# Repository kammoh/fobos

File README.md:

FOBOS
=====

Flexible Open-source workBench fOr Side-channel analysis (FOBOS) is an "acquisition to analysis" solution which includes all necessary software to control the device under test (attack) (DUT), trigger the oscilloscope, obtain the measurements and analyze them using several power analysis techniques.

FOBOS splits the Side Channel Analysis (SCA) setup into a control board, a DUT, and the SCA workstation. The firmware for the control board can be found in the folder `control`. The hardware description language files required to adapt a cryptographic algorithm to a particular FOBOS DUT are in the folder `DUT`. The `hardware` folder on the other hand contains circuit board design files for FOBOS boards such as the FOBOS Shield and several FOBOS DUTs. The `software` folder contains the scripts to run FOBOS. These python scripts run partially on the SCA workstation within a Jupyter notebook and partially on the Pynq DUT. The `docs` folder contains the FOBOS documentation.

FOBOS Control Board
-------------------
* `control`
   VHDL sources for configuring the FOBOS Control Boards. Requires Xilinx Vivado 2020.2.
   * `basys3ctrl`
     Using a Digilent Inc Basys 3 as control board and an oscilloscope for measurements.
   * `pynqctrl`
     Using a Digilent Inc PYNQ-Z1 as control board and either the FOBOS Shield or an oscilloscope for measurements.
   * `ip-repo` 
     Modules used by either control board.

FOBOS DUT
---------
* `dut`
  VHDL sources for FOBOS wrapper and pin assignments to prepare a DUT for instantiating a target algorithm.
  * `fpga_wrapper`
    Source code of the FOBOS wrapper common to all FPGA targets and the contraint files for the supported DUTs.
  * `soc_wrapper`
    Source code for system on chip boards such as Zybo.
  * `example_cores`
    Contains implementations of example algorithms required for the tutorials.
 
FOBOS Hardware
--------------
* `hardware`
  Printed Circuit Board design files for FOBOS boards. Requires KiCad.
  * `fobos-shield`
    FOBOS Shield is a data aqcuisition and benchmarking boad that can be attached to the PYNQ-Z1 controller.
  * `fobos-mtc`
    FOBOS Multi Target Connector allows simple connection of several DUT boards to the FOBOS Shield.
  * `fobos-dut`
    Contains folders for each FOBOS DUT.

FOBOS Software
--------------
* `software`
  FOBOS is controlled by a series of Python 3 scripts. They can be executed in several different ways.
  1. Command line, either on PYNQ or on a PC, tested on Windows 10 and Linux.
  1. Jupyter Notebook, either on PYNQ or on a PC, tested on Windows 10 and Linux.

  * `foboslib` contains all common FOBOS functions.
  * `notebooks` contains Jupyter notebooks that run within Jypyter Lab on a PC.
  * `pynq=notebooks` contains Jupyter notebooks that run on within Jupyter Hub on Pynq.
  * `examples` contains command line examples

Documentation
-------------

* `docs` 
  Contains the sources for the Sphinx based documentation of FOBOS and the makefile to compile it.
  All figures used for the FOBOS documentation are in the folder `docs\source\figures`.

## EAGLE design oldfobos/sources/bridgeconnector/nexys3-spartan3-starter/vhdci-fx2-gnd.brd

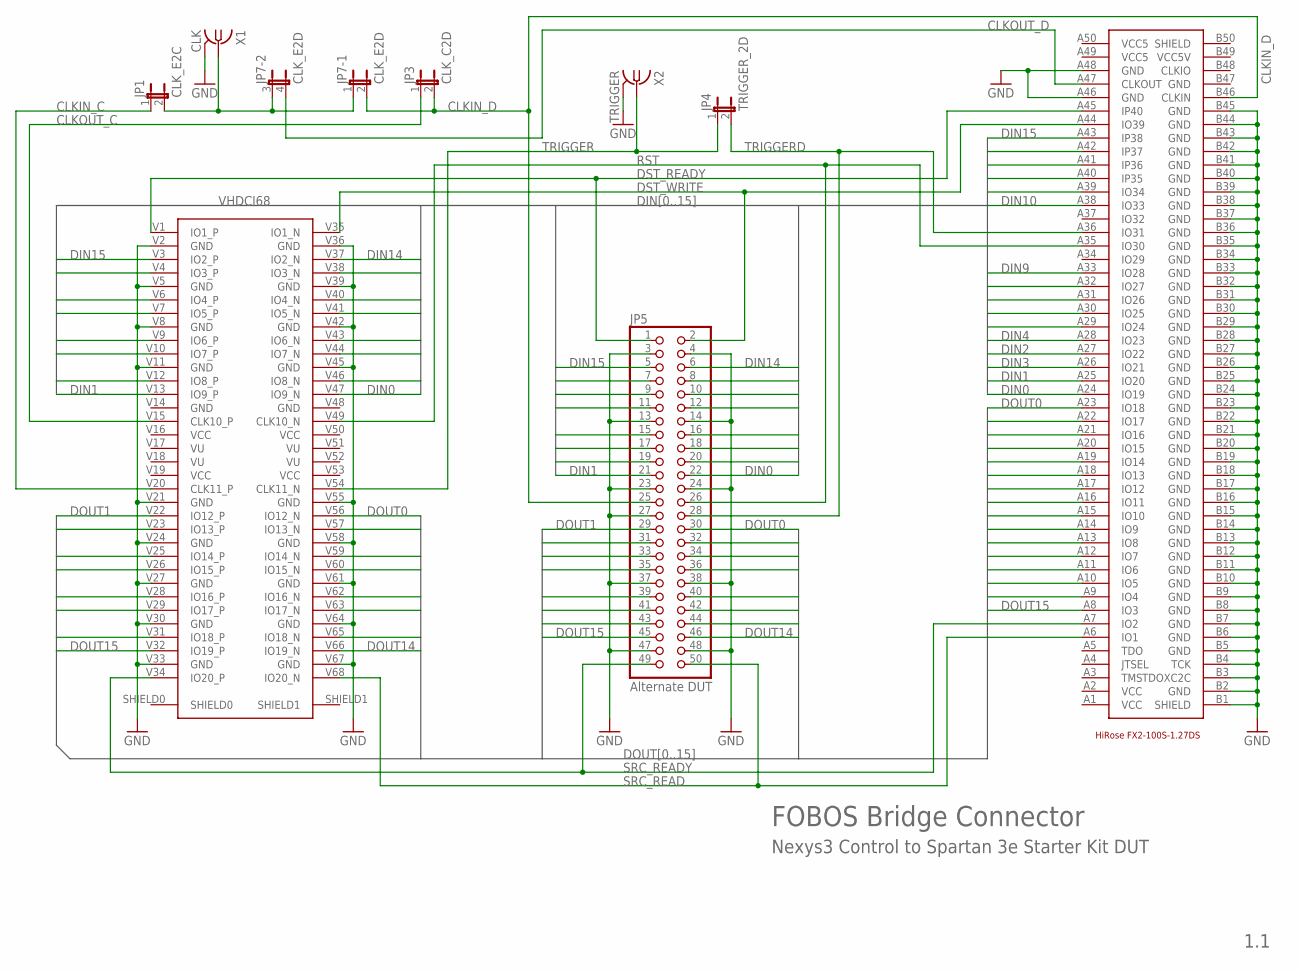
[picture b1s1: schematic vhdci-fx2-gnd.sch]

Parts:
DUT: HIROSE-FX2-100S-1.27DS; HIROSE-FX2-100
JP1: CLK_E2C; JP1
JP3: CLK_C2D; JP1
JP4: TRIGGER_2D; JP1
JP5: Alternate DUT; 2X25
JP7: CLK_E2D; JP2Q
U$2: VHDCI68
X1: CLK; BU-SMA-V
X2: TRIGGER; BU-SMA-V

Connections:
CLKIN_C: JP1.1, U$2.V20 (CLK11_P)
CLKIN_D: DUT.B46 (CLKIN), JP3.2, JP5.25, JP7.2
CLKOUT_C: JP3.1, U$2.V15 (CLK10_P)
CLKOUT_D: DUT.A47 (CLKOUT), JP7.4 (2)
DIN0: DUT.A24 (IO19), JP5.22, U$2.V47 (IO9_N)
DIN1: DUT.A25 (IO20), JP5.21, U$2.V13 (IO9_P)
DIN2: DUT.A27 (IO22), JP5.20, U$2.V46 (IO8_N)
DIN3: DUT.A26 (IO21), JP5.19, U$2.V12 (IO8_P)
DIN4: DUT.A28 (IO23), JP5.18, U$2.V44 (IO7_N)
DIN5: DUT.A29 (IO24), JP5.17, U$2.V10 (IO7_P)
DIN6: DUT.A30 (IO25), JP5.16, U$2.V43 (IO6_N)
DIN7: DUT.A31 (IO26), JP5.15, U$2.V9 (IO6_P)
DIN8: DUT.A32 (IO27), JP5.12, U$2.V41 (IO5_N)
DIN9: DUT.A33 (IO28), JP5.11, U$2.V7 (IO5_P)
DIN10: DUT.A38 (IO33), JP5.10, U$2.V40 (IO4_N)
DIN11: DUT.A39 (IO34), JP5.9, U$2.V6 (IO4_P)
DIN12: DUT.A40 (IP35), JP5.8, U$2.V38 (IO3_N)
DIN13: DUT.A41 (IP36), JP5.7, U$2.V4 (IO3_P)
DIN14: DUT.A42 (IP37), JP5.6, U$2.V37 (IO2_N)
DIN15: DUT.A43 (IP38), JP5.5, U$2.V3 (IO2_P)
DOUT0: DUT.A23 (IO18), JP5.30, U$2.V56 (IO12_N)
DOUT1: DUT.A22 (IO17), JP5.29, U$2.V22 (IO12_P)
DOUT2: DUT.A21 (IO16), JP5.32, U$2.V57 (IO13_N)
DOUT3: DUT.A20 (IO15), JP5.31, U$2.V23 (IO13_P)
DOUT4: DUT.A19 (IO14), JP5.34, U$2.V59 (IO14_N)
DOUT5: DUT.A18 (IO13), JP5.33, U$2.V25 (IO14_P)
DOUT6: DUT.A17 (IO12), JP5.36, U$2.V60 (IO15_N)
DOUT7: DUT.A16 (IO11), JP5.35, U$2.V26 (IO15_P)
DOUT8: DUT.A15 (IO10), JP5.40, U$2.V62 (IO16_N)
DOUT9: DUT.A14 (IO9), JP5.39, U$2.V28 (IO16_P)
DOUT10: DUT.A13 (IO8), JP5.42, U$2.V63 (IO17_N)
DOUT11: DUT.A12 (IO7), JP5.41, U$2.V29 (IO17_P)
DOUT12: DUT.A11 (IO6), JP5.44, U$2.V65 (IO18_N)
DOUT13: DUT.A10 (IO5), JP5.43, U$2.V31 (IO18_P)
DOUT14: DUT.A9 (IO4), JP5.46, U$2.V66 (IO19_N)
DOUT15: DUT.A8 (IO3), JP5.45, U$2.V32 (IO19_P)
DST_READY: DUT.A45 (IP40), JP5.1, U$2.V1 (IO1_P)
DST_WRITE: DUT.A44 (IO39), JP5.2, U$2.V35 (IO1_N)
GND: DUT.A46 (GND), DUT.A48 (GND), DUT.B1 (SHIELD), DUT.B2 (GND), DUT.B3 (TDOXC2C), DUT.B4 (TCK), DUT.B5 (GND), DUT.B6 (GND), DUT.B7 (GND), DUT.B8 (GND), DUT.B9 (GND), DUT.B10 (GND), DUT.B11 (GND), DUT.B12 (GND), DUT.B13 (GND), DUT.B14 (GND), DUT.B15 (GND), DUT.B16 (GND), DUT.B17 (GND), DUT.B18 (GND), DUT.B19 (GND), DUT.B20 (GND), DUT.B21 (GND), DUT.B22 (GND), DUT.B23 (GND), DUT.B24 (GND), DUT.B25 (GND), DUT.B26 (GND), DUT.B27 (GND), DUT.B28 (GND), DUT.B29 (GND), DUT.B30 (GND), DUT.B31 (GND), DUT.B32 (GND), DUT.B33 (GND), DUT.B34 (GND), DUT.B35 (GND), DUT.B36 (GND), DUT.B37 (GND), DUT.B38 (GND), DUT.B39 (GND), DUT.B40 (GND), DUT.B41 (GND), DUT.B42 (GND), DUT.B43 (GND), DUT.B44 (GND), DUT.B45 (GND), DUT.B47 (GND), JP5.3, JP5.4, JP5.13, JP5.14, JP5.23, JP5.24, JP5.27, JP5.37, JP5.38, JP5.47, JP5.48, U$2.V2 (GND), U$2.V5 (GND), U$2.V8 (GND), U$2.V11 (GND), U$2.V21 (GND), U$2.V24 (GND), U$2.V27 (GND), U$2.V30 (GND), U$2.V33 (GND), U$2.V36 (GND), U$2.V39 (GND), U$2.V42 (GND), U$2.V45 (GND), U$2.V55 (GND), U$2.V58 (GND), U$2.V61 (GND), U$2.V64 (GND), U$2.V67 (GND), X1.2 (GND), X1.3 (GND), X1.4 (GND), X1.5 (GND), X2.2 (GND), X2.3 (GND), X2.4 (GND), X2.5 (GND)
unnamed: JP1.2, JP7.1, JP7.3 (1), X1.1
RST: DUT.A35 (IO30), JP5.26, U$2.V49 (CLK10_N)
SRC_READ: DUT.A6 (IO1), JP5.50, U$2.V68 (IO20_N)
SRC_READY: DUT.A7 (IO2), JP5.49, U$2.V34 (IO20_P)
TRIGGER: JP4.1, U$2.V54 (CLK11_N), X2.1
TRIGGERD: DUT.A36 (IO31), JP4.2, JP5.28
VCC: DUT.A1 (VCC), DUT.A2 (VCC), U$2.V16 (VCC), U$2.V19 (VCC), U$2.V50 (VCC), U$2.V53 (VCC)
VCC5: DUT.A49 (VCC5), DUT.A50 (VCC5)
VCC5V: DUT.B49 (VCC5V)
VU: U$2.V17 (VU), U$2.V18 (VU), U$2.V51 (VU), U$2.V52 (VU)

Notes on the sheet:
FOBOS Bridge Connector
Nexys3 Control to Spartan 3e Starter Kit DUT
1.1

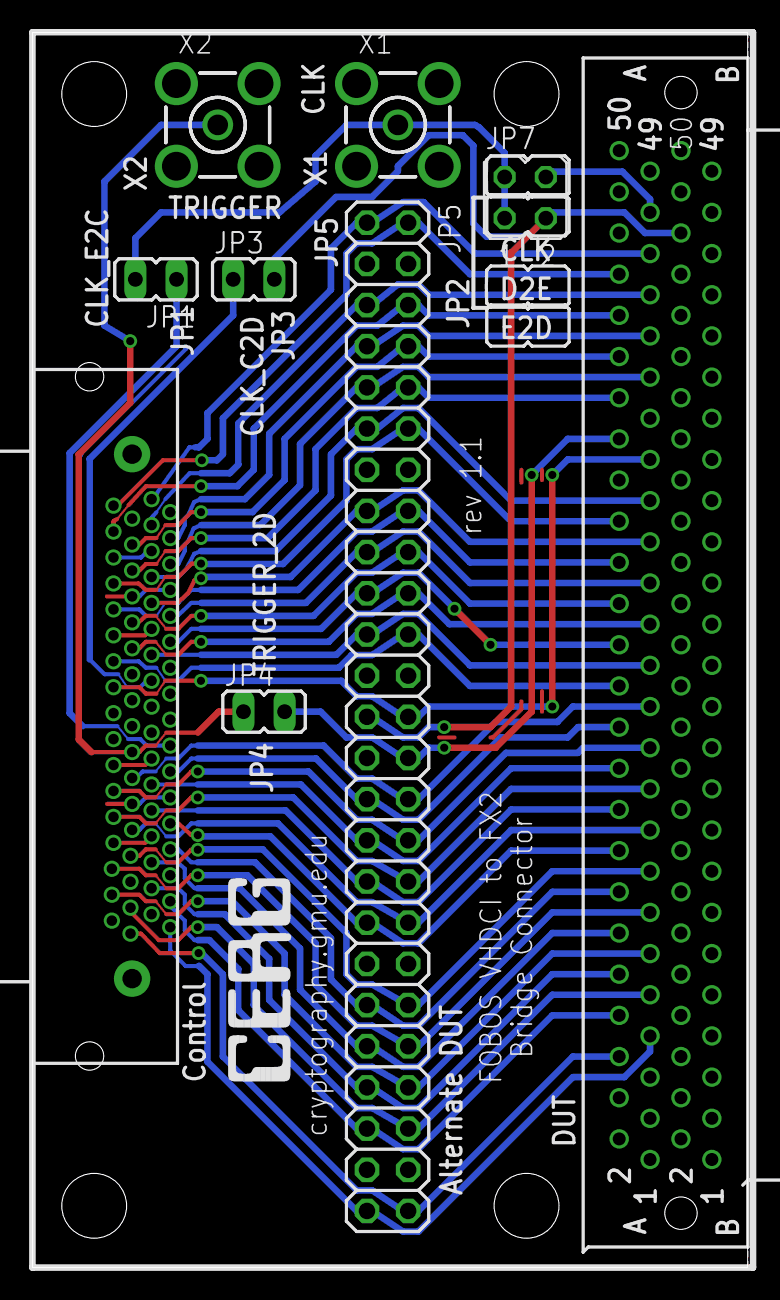
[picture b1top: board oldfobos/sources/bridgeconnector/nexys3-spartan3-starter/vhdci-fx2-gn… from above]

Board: 2 copper layers, 44.1 x 76.2 mm, 9 parts (0 on the bottom side), 48 nets.

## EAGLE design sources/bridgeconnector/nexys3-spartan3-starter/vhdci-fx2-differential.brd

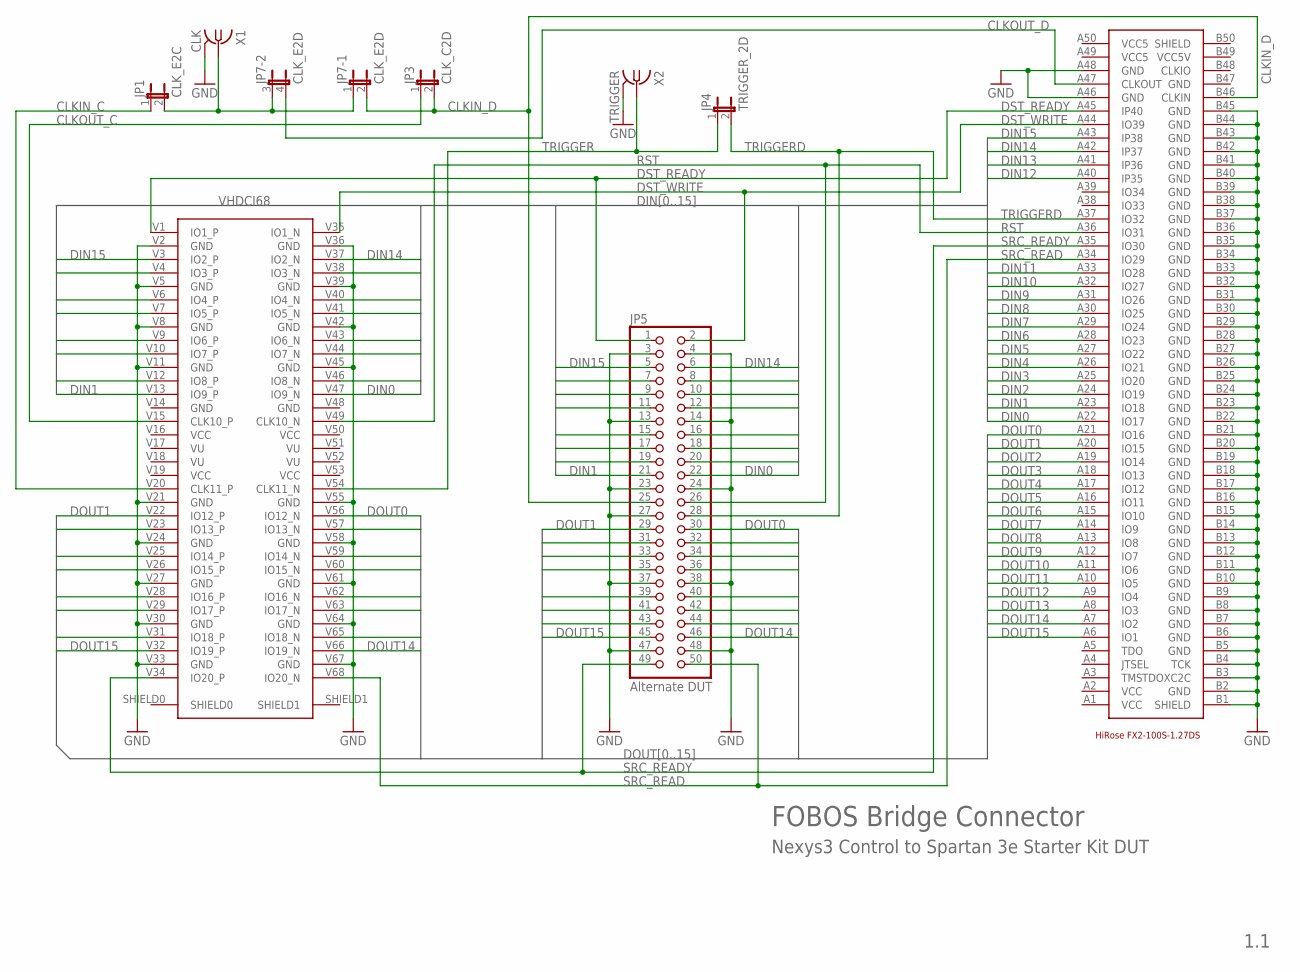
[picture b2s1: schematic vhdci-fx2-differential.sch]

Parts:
DUT: HIROSE-FX2-100S-1.27DS; HIROSE-FX2-100
JP1: CLK_E2C; JP1
JP3: CLK_C2D; JP1
JP4: TRIGGER_2D; JP1
JP5: Alternate DUT; 2X25
JP7: CLK_E2D; JP2Q
U$2: VHDCI68
X1: CLK; BU-SMA-V
X2: TRIGGER; BU-SMA-V

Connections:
CLKIN_C: JP1.1, U$2.V20 (CLK11_P)
CLKIN_D: DUT.B46 (CLKIN), JP3.2, JP5.25, JP7.2
CLKOUT_C: JP3.1, U$2.V15 (CLK10_P)
CLKOUT_D: DUT.A47 (CLKOUT), JP7.4 (2)
DIN0: DUT.A22 (IO17), JP5.22, U$2.V47 (IO9_N)
DIN1: DUT.A23 (IO18), JP5.21, U$2.V13 (IO9_P)
DIN2: DUT.A24 (IO19), JP5.20, U$2.V46 (IO8_N)
DIN3: DUT.A25 (IO20), JP5.19, U$2.V12 (IO8_P)
DIN4: DUT.A26 (IO21), JP5.18, U$2.V44 (IO7_N)
DIN5: DUT.A27 (IO22), JP5.17, U$2.V10 (IO7_P)
DIN6: DUT.A28 (IO23), JP5.16, U$2.V43 (IO6_N)
DIN7: DUT.A29 (IO24), JP5.15, U$2.V9 (IO6_P)
DIN8: DUT.A30 (IO25), JP5.12, U$2.V41 (IO5_N)
DIN9: DUT.A31 (IO26), JP5.11, U$2.V7 (IO5_P)
DIN10: DUT.A32 (IO27), JP5.10, U$2.V40 (IO4_N)
DIN11: DUT.A33 (IO28), JP5.9, U$2.V6 (IO4_P)
DIN12: DUT.A40 (IP35), JP5.8, U$2.V38 (IO3_N)
DIN13: DUT.A41 (IP36), JP5.7, U$2.V4 (IO3_P)
DIN14: DUT.A42 (IP37), JP5.6, U$2.V37 (IO2_N)
DIN15: DUT.A43 (IP38), JP5.5, U$2.V3 (IO2_P)
DOUT0: DUT.A21 (IO16), JP5.30, U$2.V56 (IO12_N)
DOUT1: DUT.A20 (IO15), JP5.29, U$2.V22 (IO12_P)
DOUT2: DUT.A19 (IO14), JP5.32, U$2.V57 (IO13_N)
DOUT3: DUT.A18 (IO13), JP5.31, U$2.V23 (IO13_P)
DOUT4: DUT.A17 (IO12), JP5.34, U$2.V59 (IO14_N)
DOUT5: DUT.A16 (IO11), JP5.33, U$2.V25 (IO14_P)
DOUT6: DUT.A15 (IO10), JP5.36, U$2.V60 (IO15_N)
DOUT7: DUT.A14 (IO9), JP5.35, U$2.V26 (IO15_P)
DOUT8: DUT.A13 (IO8), JP5.40, U$2.V62 (IO16_N)
DOUT9: DUT.A12 (IO7), JP5.39, U$2.V28 (IO16_P)
DOUT10: DUT.A11 (IO6), JP5.42, U$2.V63 (IO17_N)
DOUT11: DUT.A10 (IO5), JP5.41, U$2.V29 (IO17_P)
DOUT12: DUT.A9 (IO4), JP5.44, U$2.V65 (IO18_N)
DOUT13: DUT.A8 (IO3), JP5.43, U$2.V31 (IO18_P)
DOUT14: DUT.A7 (IO2), JP5.46, U$2.V66 (IO19_N)
DOUT15: DUT.A6 (IO1), JP5.45, U$2.V32 (IO19_P)
DST_READY: DUT.A45 (IP40), JP5.1, U$2.V1 (IO1_P)
DST_WRITE: DUT.A44 (IO39), JP5.2, U$2.V35 (IO1_N)
GND: DUT.A46 (GND), DUT.A48 (GND), DUT.B1 (SHIELD), DUT.B2 (GND), DUT.B3 (TDOXC2C), DUT.B4 (TCK), DUT.B5 (GND), DUT.B6 (GND), DUT.B7 (GND), DUT.B8 (GND), DUT.B9 (GND), DUT.B10 (GND), DUT.B11 (GND), DUT.B12 (GND), DUT.B13 (GND), DUT.B14 (GND), DUT.B15 (GND), DUT.B16 (GND), DUT.B17 (GND), DUT.B18 (GND), DUT.B19 (GND), DUT.B20 (GND), DUT.B21 (GND), DUT.B22 (GND), DUT.B23 (GND), DUT.B24 (GND), DUT.B25 (GND), DUT.B26 (GND), DUT.B27 (GND), DUT.B28 (GND), DUT.B29 (GND), DUT.B30 (GND), DUT.B31 (GND), DUT.B32 (GND), DUT.B33 (GND), DUT.B34 (GND), DUT.B35 (GND), DUT.B36 (GND), DUT.B37 (GND), DUT.B38 (GND), DUT.B39 (GND), DUT.B40 (GND), DUT.B41 (GND), DUT.B42 (GND), DUT.B43 (GND), DUT.B44 (GND), DUT.B45 (GND), DUT.B47 (GND), JP5.3, JP5.4, JP5.13, JP5.14, JP5.23, JP5.24, JP5.27, JP5.37, JP5.38, JP5.47, JP5.48, U$2.V2 (GND), U$2.V5 (GND), U$2.V8 (GND), U$2.V11 (GND), U$2.V21 (GND), U$2.V24 (GND), U$2.V27 (GND), U$2.V30 (GND), U$2.V33 (GND), U$2.V36 (GND), U$2.V39 (GND), U$2.V42 (GND), U$2.V45 (GND), U$2.V55 (GND), U$2.V58 (GND), U$2.V61 (GND), U$2.V64 (GND), U$2.V67 (GND), X1.2 (GND), X1.3 (GND), X1.4 (GND), X1.5 (GND), X2.2 (GND), X2.3 (GND), X2.4 (GND), X2.5 (GND)
unnamed: JP1.2, JP7.1, JP7.3 (1), X1.1
RST: DUT.A36 (IO31), JP5.26, U$2.V49 (CLK10_N)
SRC_READ: DUT.A34 (IO29), JP5.50, U$2.V68 (IO20_N)
SRC_READY: DUT.A35 (IO30), JP5.49, U$2.V34 (IO20_P)
TRIGGER: JP4.1, U$2.V54 (CLK11_N), X2.1
TRIGGERD: DUT.A37 (IO32), JP4.2, JP5.28
VCC: DUT.A1 (VCC), DUT.A2 (VCC), U$2.V16 (VCC), U$2.V19 (VCC), U$2.V50 (VCC), U$2.V53 (VCC)
VCC5: DUT.A49 (VCC5), DUT.A50 (VCC5)
VCC5V: DUT.B49 (VCC5V)
VU: U$2.V17 (VU), U$2.V18 (VU), U$2.V51 (VU), U$2.V52 (VU)

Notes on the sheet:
FOBOS Bridge Connector
Nexys3 Control to Spartan 3e Starter Kit DUT
1.1

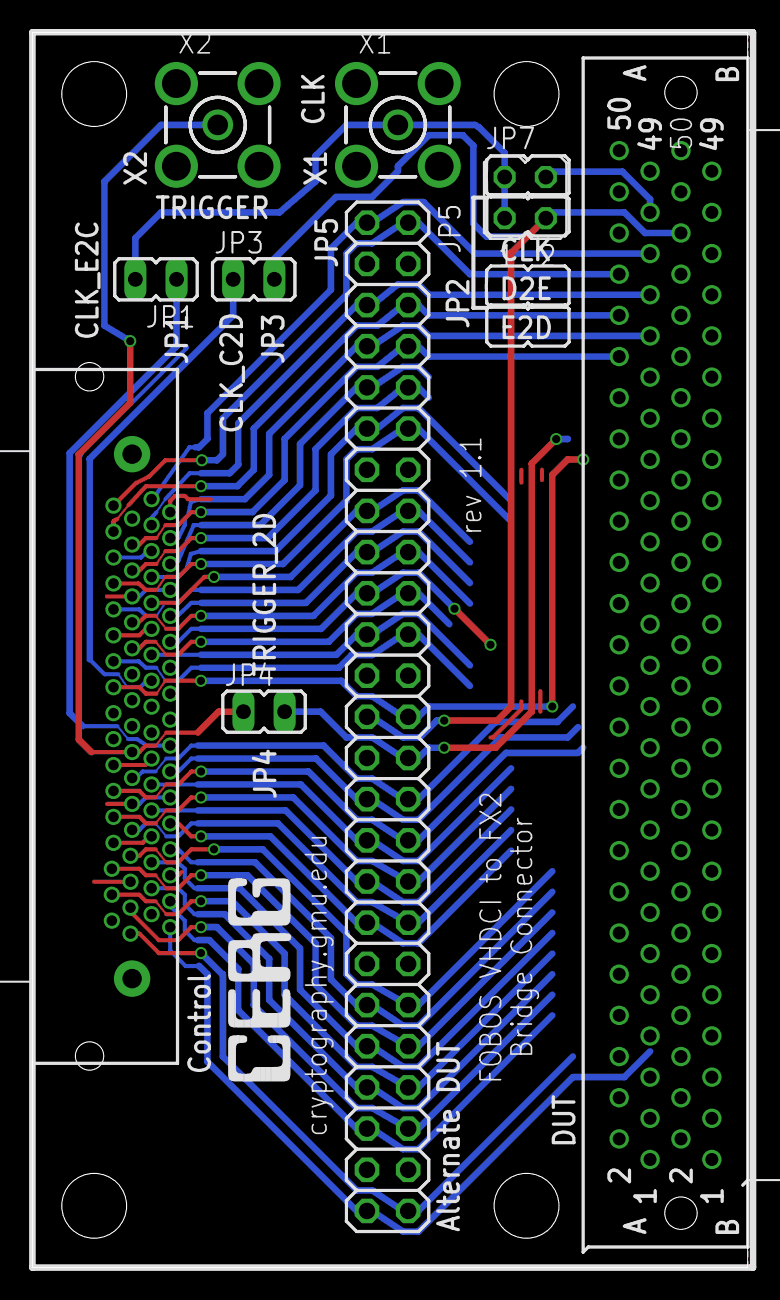
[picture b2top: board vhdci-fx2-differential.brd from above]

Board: 2 copper layers, 44.1 x 76.2 mm, 9 parts (0 on the bottom side), 48 nets.

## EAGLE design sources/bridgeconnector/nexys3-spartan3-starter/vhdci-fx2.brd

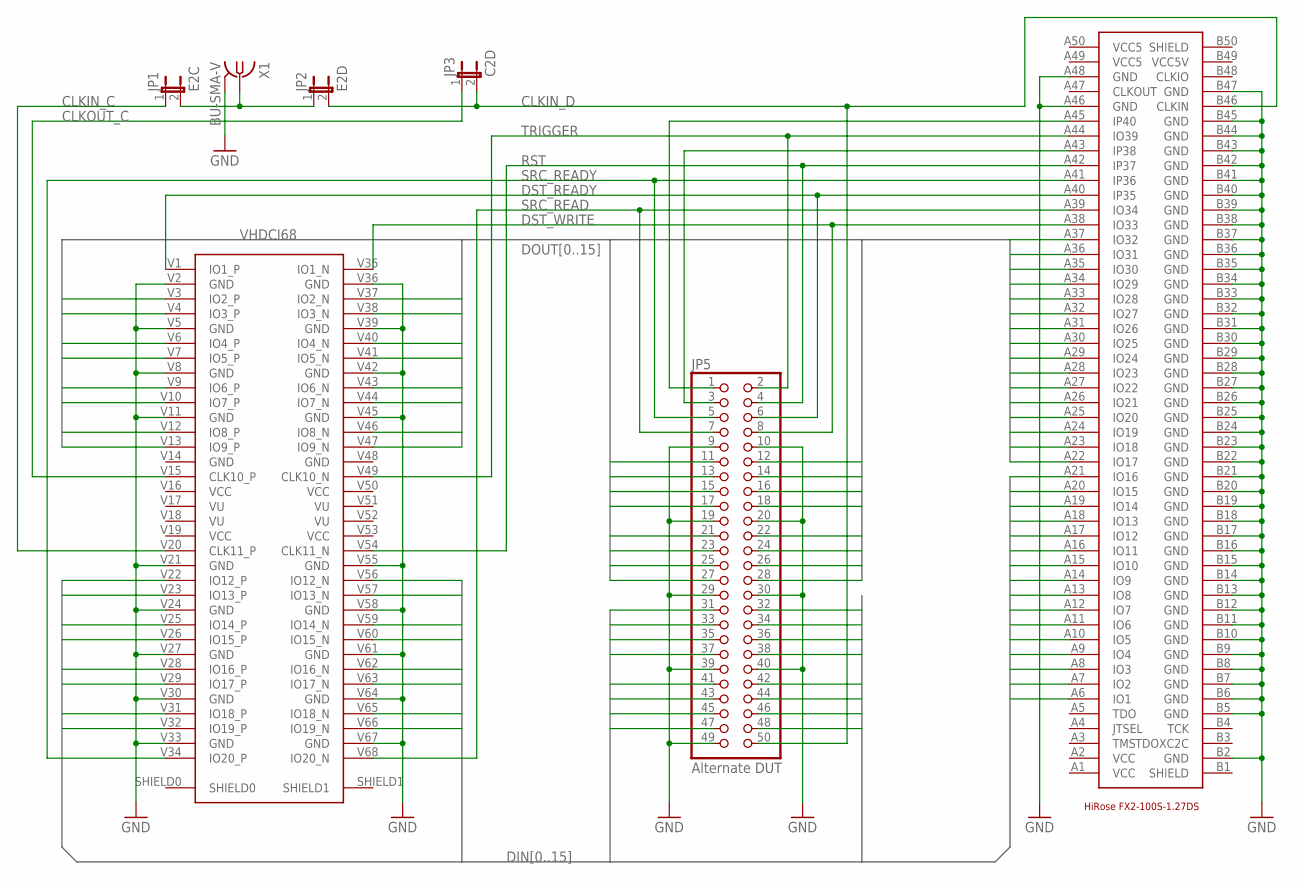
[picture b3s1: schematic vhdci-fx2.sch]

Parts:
JP1: E2C; JP1
JP2: E2D; JP1
JP3: C2D; JP1
JP5: Alternate DUT; 2X25
U$1: HIROSE-FX2-100S-1.27DS; HIROSE-FX2-100
U$2: VHDCI68
X1: BU-SMA-V

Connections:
CLKIN_C: JP1.1, U$2.V20 (CLK11_P)
CLKIN_D: JP2.2, JP3.2, JP5.50, U$1.B46 (CLKIN)
CLKOUT_C: JP3.1, U$2.V15 (CLK10_P)
DIN0: JP5.48, U$1.A6 (IO1), U$2.V66 (IO19_N)
DIN1: JP5.47, U$1.A7 (IO2), U$2.V32 (IO19_P)
DIN2: JP5.46, U$1.A8 (IO3), U$2.V65 (IO18_N)
DIN3: JP5.45, U$1.A9 (IO4), U$2.V31 (IO18_P)
DIN4: JP5.44, U$1.A10 (IO5), U$2.V63 (IO17_N)
DIN5: JP5.43, U$1.A11 (IO6), U$2.V29 (IO17_P)
DIN6: JP5.42, U$1.A12 (IO7), U$2.V62 (IO16_N)
DIN7: JP5.41, U$1.A13 (IO8), U$2.V28 (IO16_P)
DIN8: JP5.38, U$1.A14 (IO9), U$2.V60 (IO15_N)
DIN9: JP5.37, U$1.A15 (IO10), U$2.V26 (IO15_P)
DIN10: JP5.36, U$1.A16 (IO11), U$2.V59 (IO14_N)
DIN11: JP5.35, U$1.A17 (IO12), U$2.V25 (IO14_P)
DIN12: JP5.34, U$1.A18 (IO13), U$2.V57 (IO13_N)
DIN13: JP5.33, U$1.A19 (IO14), U$2.V23 (IO13_P)
DIN14: JP5.32, U$1.A20 (IO15), U$2.V56 (IO12_N)
DIN15: JP5.31, U$1.A21 (IO16), U$2.V22 (IO12_P)
DOUT0: JP5.28, U$1.A22 (IO17), U$2.V47 (IO9_N)
DOUT1: JP5.27, U$1.A23 (IO18), U$2.V13 (IO9_P)
DOUT2: JP5.26, U$1.A24 (IO19), U$2.V46 (IO8_N)
DOUT3: JP5.25, U$1.A25 (IO20), U$2.V12 (IO8_P)
DOUT4: JP5.24, U$1.A26 (IO21), U$2.V44 (IO7_N)
DOUT5: JP5.23, U$1.A27 (IO22), U$2.V10 (IO7_P)
DOUT6: JP5.22, U$1.A28 (IO23), U$2.V43 (IO6_N)
DOUT7: JP5.21, U$1.A29 (IO24), U$2.V9 (IO6_P)
DOUT8: JP5.18, U$1.A30 (IO25), U$2.V41 (IO5_N)
DOUT9: JP5.17, U$1.A31 (IO26), U$2.V7 (IO5_P)
DOUT10: JP5.16, U$1.A32 (IO27), U$2.V40 (IO4_N)
DOUT11: JP5.15, U$1.A33 (IO28), U$2.V6 (IO4_P)
DOUT12: JP5.14, U$1.A34 (IO29), U$2.V38 (IO3_N)
DOUT13: JP5.13, U$1.A35 (IO30), U$2.V4 (IO3_P)
DOUT14: JP5.12, U$1.A36 (IO31), U$2.V37 (IO2_N)
DOUT15: JP5.11, U$1.A37 (IO32), U$2.V3 (IO2_P)
DST_READY: JP5.6, U$1.A40 (IP35), U$2.V1 (IO1_P)
DST_WRITE: JP5.8, U$1.A38 (IO33), U$2.V35 (IO1_N)
GND: JP5.9, JP5.10, JP5.19, JP5.20, JP5.29, JP5.30, JP5.39, JP5.40, JP5.49, U$1.A46 (GND), U$1.A48 (GND), U$1.B2 (GND), U$1.B5 (GND), U$1.B6 (GND), U$1.B7 (GND), U$1.B8 (GND), U$1.B9 (GND), U$1.B10 (GND), U$1.B11 (GND), U$1.B12 (GND), U$1.B13 (GND), U$1.B14 (GND), U$1.B15 (GND), U$1.B16 (GND), U$1.B17 (GND), U$1.B18 (GND), U$1.B19 (GND), U$1.B20 (GND), U$1.B21 (GND), U$1.B22 (GND), U$1.B23 (GND), U$1.B24 (GND), U$1.B25 (GND), U$1.B26 (GND), U$1.B27 (GND), U$1.B28 (GND), U$1.B29 (GND), U$1.B30 (GND), U$1.B31 (GND), U$1.B32 (GND), U$1.B33 (GND), U$1.B34 (GND), U$1.B35 (GND), U$1.B36 (GND), U$1.B37 (GND), U$1.B38 (GND), U$1.B39 (GND), U$1.B40 (GND), U$1.B41 (GND), U$1.B42 (GND), U$1.B43 (GND), U$1.B44 (GND), U$1.B45 (GND), U$1.B47 (GND), U$2.V2 (GND), U$2.V5 (GND), U$2.V8 (GND), U$2.V11 (GND), U$2.V21 (GND), U$2.V24 (GND), U$2.V27 (GND), U$2.V30 (GND), U$2.V33 (GND), U$2.V36 (GND), U$2.V39 (GND), U$2.V42 (GND), U$2.V45 (GND), U$2.V55 (GND), U$2.V58 (GND), U$2.V61 (GND), U$2.V64 (GND), U$2.V67 (GND), X1.2 (GND), X1.3 (GND), X1.4 (GND), X1.5 (GND)
unnamed: JP1.2, JP2.1, X1.1
unnamed: JP5.1, U$1.A45 (IP40)
unnamed: JP5.3, U$1.A43 (IP38)
RST: JP5.4, U$1.A42 (IP37), U$2.V54 (CLK11_N)
SRC_READ: JP5.7, U$1.A39 (IO34), U$2.V68 (IO20_N)
SRC_READY: JP5.5, U$1.A41 (IP36), U$2.V34 (IO20_P)
TRIGGER: JP5.2, U$1.A44 (IO39), U$2.V49 (CLK10_N)
VCC: U$1.A1 (VCC), U$1.A2 (VCC), U$2.V16 (VCC), U$2.V19 (VCC), U$2.V50 (VCC), U$2.V53 (VCC)
VCC5: U$1.A49 (VCC5), U$1.A50 (VCC5)
VCC5V: U$1.B49 (VCC5V)
VU: U$2.V17 (VU), U$2.V18 (VU), U$2.V51 (VU), U$2.V52 (VU)

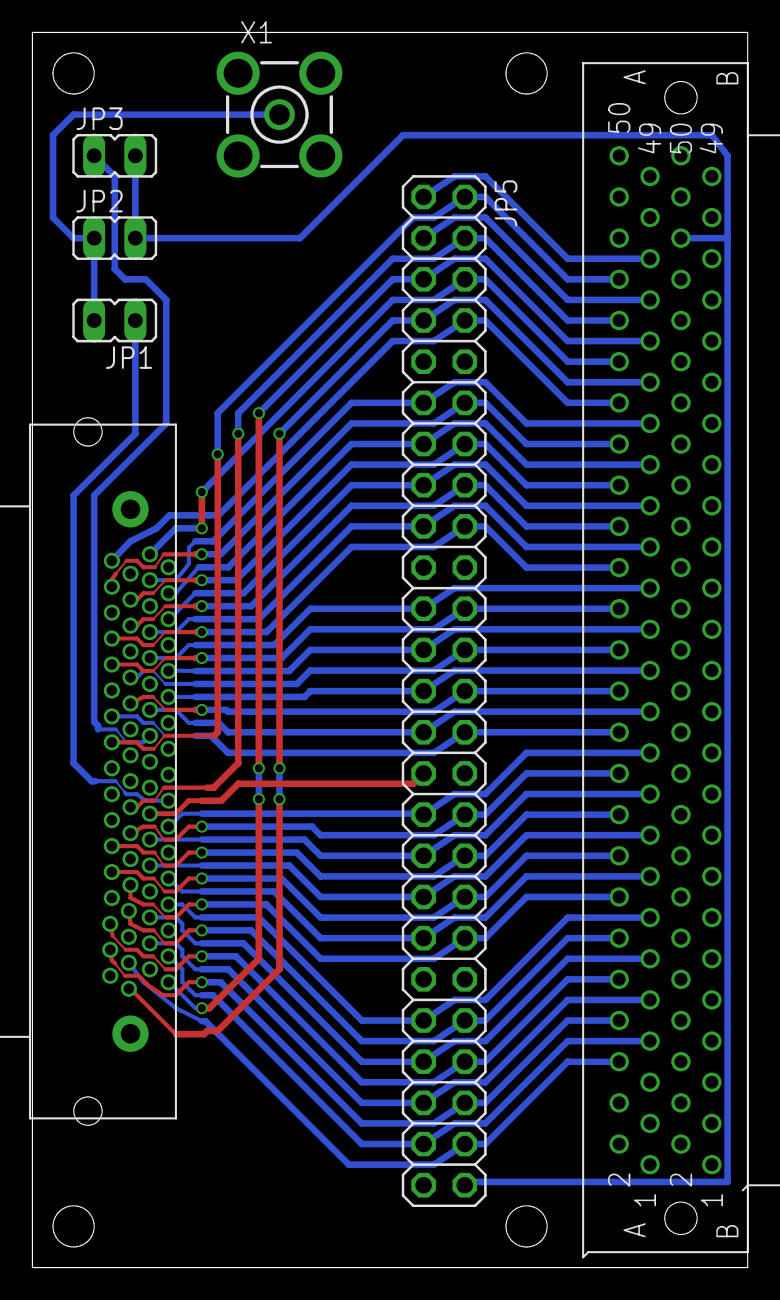
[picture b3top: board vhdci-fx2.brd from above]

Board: 2 copper layers, 44.1 x 76.2 mm, 7 parts (0 on the bottom side), 48 nets.

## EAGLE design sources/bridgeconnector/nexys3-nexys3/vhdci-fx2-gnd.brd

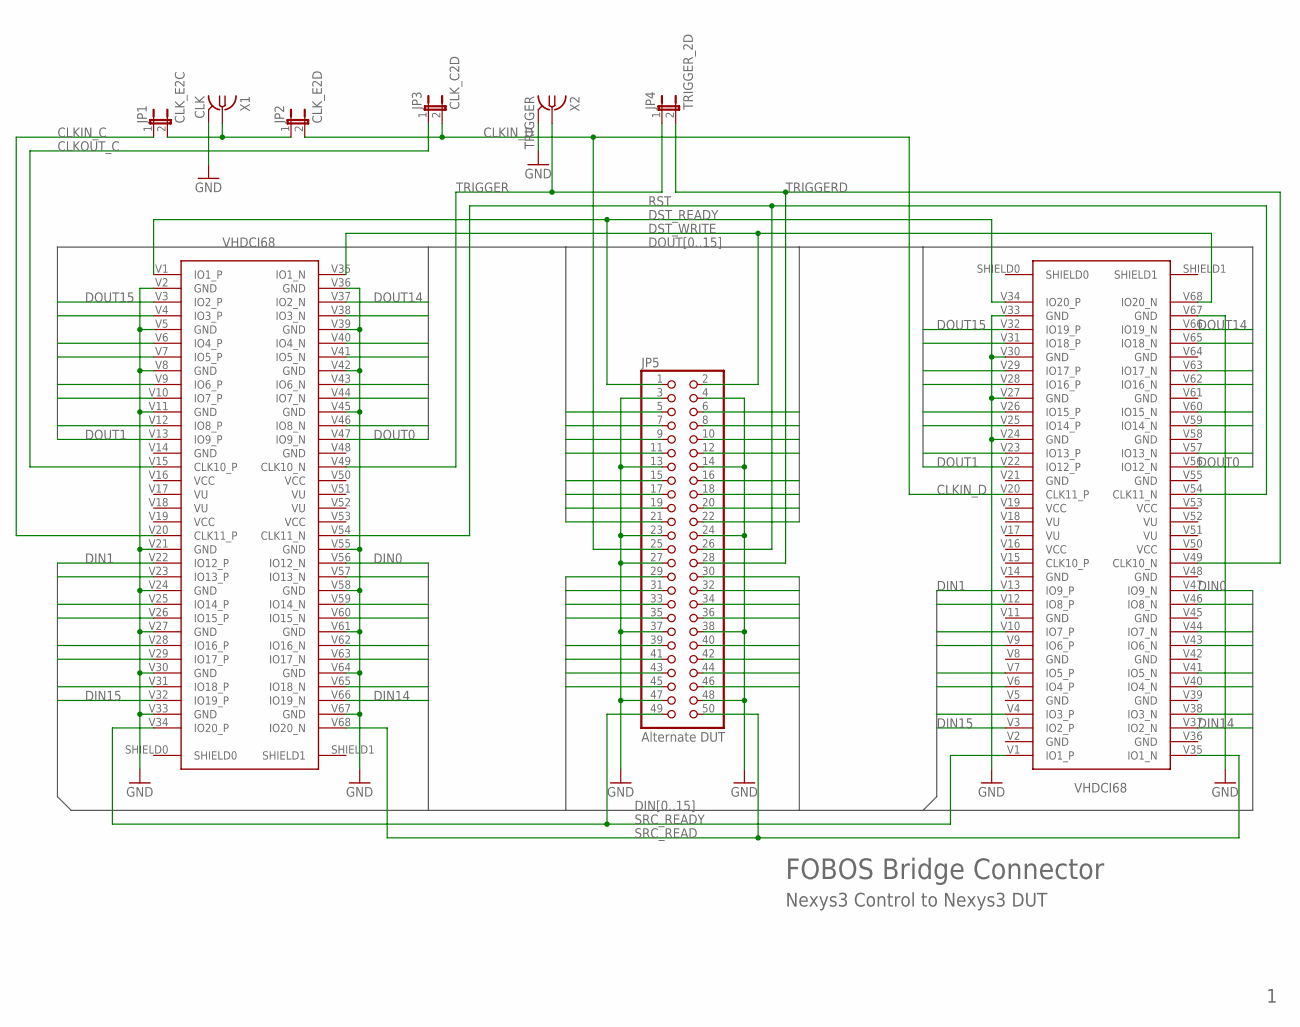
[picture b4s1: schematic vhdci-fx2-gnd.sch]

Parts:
JP1: CLK_E2C; JP1
JP2: CLK_E2D; JP1
JP3: CLK_C2D; JP1
JP4: TRIGGER_2D; JP1
JP5: Alternate DUT; 2X25
U$1, U$2: VHDCI68
X1: CLK; BU-SMA-V
X2: TRIGGER; BU-SMA-V

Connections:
CLKIN_C: JP1.1, U$2.V20 (CLK11_P)
CLKIN_D: JP2.2, JP3.2, JP5.25, U$1.V20 (CLK11_P)
CLKOUT_C: JP3.1, U$2.V15 (CLK10_P)
DIN0: JP5.30, U$1.V47 (IO9_N), U$2.V56 (IO12_N)
DIN1: JP5.29, U$1.V13 (IO9_P), U$2.V22 (IO12_P)
DIN2: JP5.32, U$1.V46 (IO8_N), U$2.V57 (IO13_N)
DIN3: JP5.31, U$1.V12 (IO8_P), U$2.V23 (IO13_P)
DIN4: JP5.34, U$1.V44 (IO7_N), U$2.V59 (IO14_N)
DIN5: JP5.33, U$1.V10 (IO7_P), U$2.V25 (IO14_P)
DIN6: JP5.36, U$1.V43 (IO6_N), U$2.V60 (IO15_N)
DIN7: JP5.35, U$1.V9 (IO6_P), U$2.V26 (IO15_P)
DIN8: JP5.40, U$1.V41 (IO5_N), U$2.V62 (IO16_N)
DIN9: JP5.39, U$1.V7 (IO5_P), U$2.V28 (IO16_P)
DIN10: JP5.42, U$1.V40 (IO4_N), U$2.V63 (IO17_N)
DIN11: JP5.41, U$1.V6 (IO4_P), U$2.V29 (IO17_P)
DIN12: JP5.44, U$1.V38 (IO3_N), U$2.V65 (IO18_N)
DIN13: JP5.43, U$1.V4 (IO3_P), U$2.V31 (IO18_P)
DIN14: JP5.46, U$1.V37 (IO2_N), U$2.V66 (IO19_N)
DIN15: JP5.45, U$1.V3 (IO2_P), U$2.V32 (IO19_P)
DOUT0: JP5.22, U$1.V56 (IO12_N), U$2.V47 (IO9_N)
DOUT1: JP5.21, U$1.V22 (IO12_P), U$2.V13 (IO9_P)
DOUT2: JP5.20, U$1.V57 (IO13_N), U$2.V46 (IO8_N)
DOUT3: JP5.19, U$1.V23 (IO13_P), U$2.V12 (IO8_P)
DOUT4: JP5.18, U$1.V59 (IO14_N), U$2.V44 (IO7_N)
DOUT5: JP5.17, U$1.V25 (IO14_P), U$2.V10 (IO7_P)
DOUT6: JP5.16, U$1.V60 (IO15_N), U$2.V43 (IO6_N)
DOUT7: JP5.15, U$1.V26 (IO15_P), U$2.V9 (IO6_P)
DOUT8: JP5.12, U$1.V62 (IO16_N), U$2.V41 (IO5_N)
DOUT9: JP5.11, U$1.V28 (IO16_P), U$2.V7 (IO5_P)
DOUT10: JP5.10, U$1.V63 (IO17_N), U$2.V40 (IO4_N)
DOUT11: JP5.9, U$1.V29 (IO17_P), U$2.V6 (IO4_P)
DOUT12: JP5.8, U$1.V65 (IO18_N), U$2.V38 (IO3_N)
DOUT13: JP5.7, U$1.V31 (IO18_P), U$2.V4 (IO3_P)
DOUT14: JP5.6, U$1.V66 (IO19_N), U$2.V37 (IO2_N)
DOUT15: JP5.5, U$1.V32 (IO19_P), U$2.V3 (IO2_P)
DST_READY: JP5.1, U$1.V34 (IO20_P), U$2.V1 (IO1_P)
DST_WRITE: JP5.2, U$1.V68 (IO20_N), U$2.V35 (IO1_N)
GND: JP5.3, JP5.4, JP5.13, JP5.14, JP5.23, JP5.24, JP5.27, JP5.37, JP5.38, JP5.47, JP5.48, U$1.V24 (GND), U$1.V27 (GND), U$1.V30 (GND), U$1.V33 (GND), U$1.V67 (GND), U$2.V2 (GND), U$2.V5 (GND), U$2.V8 (GND), U$2.V11 (GND), U$2.V21 (GND), U$2.V24 (GND), U$2.V27 (GND), U$2.V30 (GND), U$2.V33 (GND), U$2.V36 (GND), U$2.V39 (GND), U$2.V42 (GND), U$2.V45 (GND), U$2.V55 (GND), U$2.V58 (GND), U$2.V61 (GND), U$2.V64 (GND), U$2.V67 (GND), X1.2 (GND), X1.3 (GND), X1.4 (GND), X1.5 (GND), X2.2 (GND), X2.3 (GND), X2.4 (GND), X2.5 (GND)
unnamed: JP1.2, JP2.1, X1.1
RST: JP5.26, U$1.V54 (CLK11_N), U$2.V54 (CLK11_N)
SRC_READ: JP5.50, U$1.V35 (IO1_N), U$2.V68 (IO20_N)
SRC_READY: JP5.49, U$1.V1 (IO1_P), U$2.V34 (IO20_P)
TRIGGER: JP4.1, U$2.V49 (CLK10_N), X2.1
TRIGGERD: JP4.2, JP5.28, U$1.V49 (CLK10_N)
VCC: U$1.V16 (VCC), U$1.V19 (VCC), U$1.V50 (VCC), U$1.V53 (VCC), U$2.V16 (VCC), U$2.V19 (VCC), U$2.V50 (VCC), U$2.V53 (VCC)
VU: U$1.V17 (VU), U$1.V18 (VU), U$1.V51 (VU), U$1.V52 (VU), U$2.V17 (VU), U$2.V18 (VU), U$2.V51 (VU), U$2.V52 (VU)

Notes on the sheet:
FOBOS Bridge Connector
Nexys3 Control to Nexys3 DUT

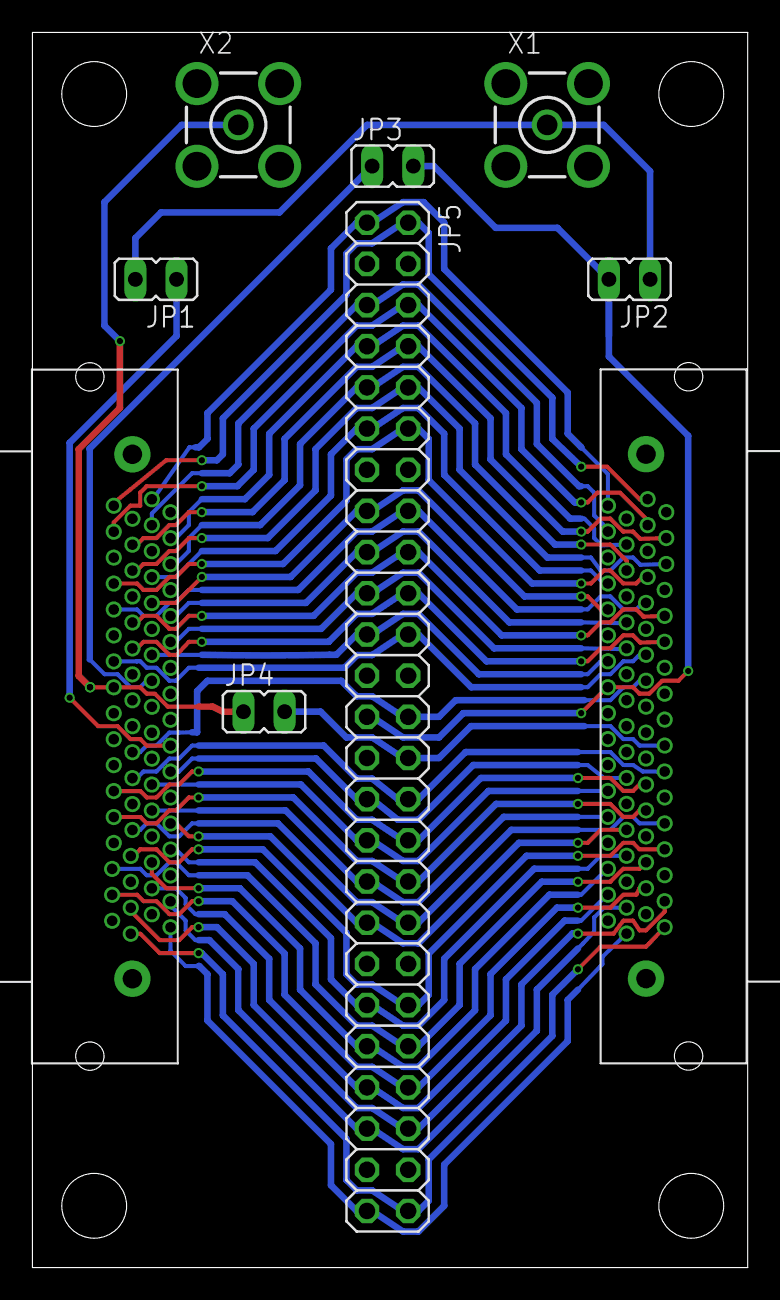
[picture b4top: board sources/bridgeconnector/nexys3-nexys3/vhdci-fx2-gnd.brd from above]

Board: 2 copper layers, 44.1 x 76.2 mm, 9 parts (0 on the bottom side), 46 nets.

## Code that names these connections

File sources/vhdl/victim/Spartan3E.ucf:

#########################################################
### SPARTAN-3E STARTER KIT BOARD DUT CONSTRAINTS FILE ###
#########################################################

# ==== FX2 Connector (FX2) ====
# ==================== Data in from Control ===================================

NET "datain<15>"   LOC = "B15" | IOSTANDARD = LVCMOS33 | SLEW = FAST | DRIVE = 8 ;    
NET "datain<14>"   LOC = "A15" | IOSTANDARD = LVCMOS33 | SLEW = FAST | DRIVE = 8 ; 
NET "datain<13>"   LOC = "C12" | IOSTANDARD = LVCMOS33 | SLEW = FAST | DRIVE = 8 ;  
NET "datain<12>"   LOC = "D12" | IOSTANDARD = LVCMOS33 | SLEW = FAST | DRIVE = 8 ; 
NET "datain<11>"   LOC = "B16" | IOSTANDARD = LVCMOS33 | SLEW = FAST | DRIVE = 8 ; 
NET "datain<10>"   LOC = "A16" | IOSTANDARD = LVCMOS33 | SLEW = FAST | DRIVE = 8 ; 
NET "datain<9>"    LOC = "D14" | IOSTANDARD = LVCMOS33 | SLEW = FAST | DRIVE = 8 ; 
NET "datain<8>"    LOC = "C14" | IOSTANDARD = LVCMOS33 | SLEW = FAST | DRIVE = 8 ; 
NET "datain<7>"    LOC = "B14" | IOSTANDARD = LVCMOS33 | SLEW = FAST | DRIVE = 8 ; 
NET "datain<6>"    LOC = "A14" | IOSTANDARD = LVCMOS33 | SLEW = FAST | DRIVE = 8 ; 
NET "datain<5>"    LOC = "B13" | IOSTANDARD = LVCMOS33 | SLEW = FAST | DRIVE = 8 ; 
NET "datain<4>"    LOC = "A13" | IOSTANDARD = LVCMOS33 | SLEW = FAST | DRIVE = 8 ; 
NET "datain<3>"    LOC = "F12" | IOSTANDARD = LVCMOS33 | SLEW = FAST | DRIVE = 8 ; 
NET "datain<2>"    LOC = "E12" | IOSTANDARD = LVCMOS33 | SLEW = FAST | DRIVE = 8 ; 
NET "datain<1>"    LOC = "E11" | IOSTANDARD = LVCMOS33 | SLEW = FAST | DRIVE = 8 ;
NET "datain<0>"    LOC = "F11" | IOSTANDARD = LVCMOS33 | SLEW = FAST | DRIVE = 8 ;

# ===================== Data out to Control  =================================== 
NET "dataout<0>"   LOC = "C11" | IOSTANDARD = LVCMOS33 | SLEW = FAST | DRIVE = 8 ;
NET "dataout<1>"   LOC = "D11" | IOSTANDARD = LVCMOS33 | SLEW = FAST | DRIVE = 8 ;
NET "dataout<2>"   LOC = "E9"  | IOSTANDARD = LVCMOS33 | SLEW = FAST | DRIVE = 8 ;
NET "dataout<3>"   LOC = "F9"  | IOSTANDARD = LVCMOS33 | SLEW = FAST | DRIVE = 8 ;
NET "dataout<4>"   LOC = "E8"  | IOSTANDARD = LVCMOS33 | SLEW = FAST | DRIVE = 8 ;
NET "dataout<5>"   LOC = "F8"  | IOSTANDARD = LVCMOS33 | SLEW = FAST | DRIVE = 8 ;
NET "dataout<6>"   LOC = "C7"  | IOSTANDARD = LVCMOS33 | SLEW = FAST | DRIVE = 8 ; 
NET "dataout<7>"   LOC = "D7"  | IOSTANDARD = LVCMOS33 | SLEW = FAST | DRIVE = 8 ;
NET "dataout<8>"   LOC = "F7"  | IOSTANDARD = LVCMOS33 | SLEW = FAST | DRIVE = 8 ;
NET "dataout<9>"   LOC = "E7"  | IOSTANDARD = LVCMOS33 | SLEW = FAST | DRIVE = 8 ;
NET "dataout<10>"  LOC = "B6"  | IOSTANDARD = LVCMOS33 | SLEW = FAST | DRIVE = 8 ;
NET "dataout<11>"  LOC = "A6"  | IOSTANDARD = LVCMOS33 | SLEW = FAST | DRIVE = 8 ;
NET "dataout<12>"  LOC = "C5"  | IOSTANDARD = LVCMOS33 | SLEW = FAST | DRIVE = 8 ;
NET "dataout<13>"  LOC = "D5"  | IOSTANDARD = LVCMOS33 | SLEW = FAST | DRIVE = 8 ;
NET "dataout<14>"  LOC = "A4"  | IOSTANDARD = LVCMOS33 | SLEW = FAST | DRIVE = 8 ;
NET "dataout<15>"  LOC = "B4"  | IOSTANDARD = LVCMOS33 | SLEW = FAST | DRIVE = 8 ;   

# ===================== CONTROL SIGNALS =========================================
NET "src_ready" LOC = "C4"  | IOSTANDARD = LVCMOS33 | SLEW = FAST | DRIVE = 8 ;  
NET "src_read"  LOC = "E13" | IOSTANDARD = LVCMOS33 | SLEW = FAST | DRIVE = 8 ;  
NET "dst_ready" LOC = "C15" | IOSTANDARD = LVCMOS33 | SLEW = FAST | DRIVE = 8 ; 
NET "dst_write" LOC = "C3"  | IOSTANDARD = LVCMOS33 | SLEW = FAST | DRIVE = 8 ;
NET "reset"       LOC = "B11" | IOSTANDARD = LVCMOS33 | SLEW = FAST | DRIVE = 8 ; 
#NET "trigger"   LOC = "A11" | IOSTANDARD = LVCMOS33 | SLEW = FAST | DRIVE = 8 ; 

# ======================== CLOCK SIGNAL ==================================================================
NET "clock"       LOC = "E10"; # Clock
